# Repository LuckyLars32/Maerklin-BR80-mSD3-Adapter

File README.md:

# Maerklin-BR80-mSD3-Adapter
Adapterplatiene und Schallkapsel für den Einbau eines mSD3 Decoders in die Märklin BR 80.   
Die Platine habe ich mit KiCAD Version 7.X erstellt.   
Die Schallkapsel habe ich mit einer 0.4er Düse, 0.2mm Layerhöhe und 50% Infill gedruckt.   

# Materialliste / BOM:
2x LED 3.0mm (Warm-) weiß    
2x Widerstand 2,2 - 3,3 kΩ Bauform 1206 (3216 metrisch) je nach Präferenz und LED    
1x 24 Pin Steckleiste (Push-Pull) gerade mit 1,27mm Raster   
1x Keramikkondensator 1206 (3216 metrisch) 1UF   
1x Märklin mSD3 oder anderer Sounddecoder mit NEM 660 Schnitstelle   
1x 15x11x3mm Lautsprecher 4-8 Ohm   

# Zusammenbau
Einbauseite immer wie Bedruckung auf der Platiene.   
Die Wiederstände R1, R2, R3, R4 werden mit den 4x Widerstand 2,2 kΩ Bauform 0207 bestückt.   
Die NEM660 Schnittstelle wird mit der 24 Pin Steckleiste mit 1,27mm Raster bestückt.   
Der Keramikkondensator 1206 mit 1UF muss auf die Pads neben R1 und AUX4

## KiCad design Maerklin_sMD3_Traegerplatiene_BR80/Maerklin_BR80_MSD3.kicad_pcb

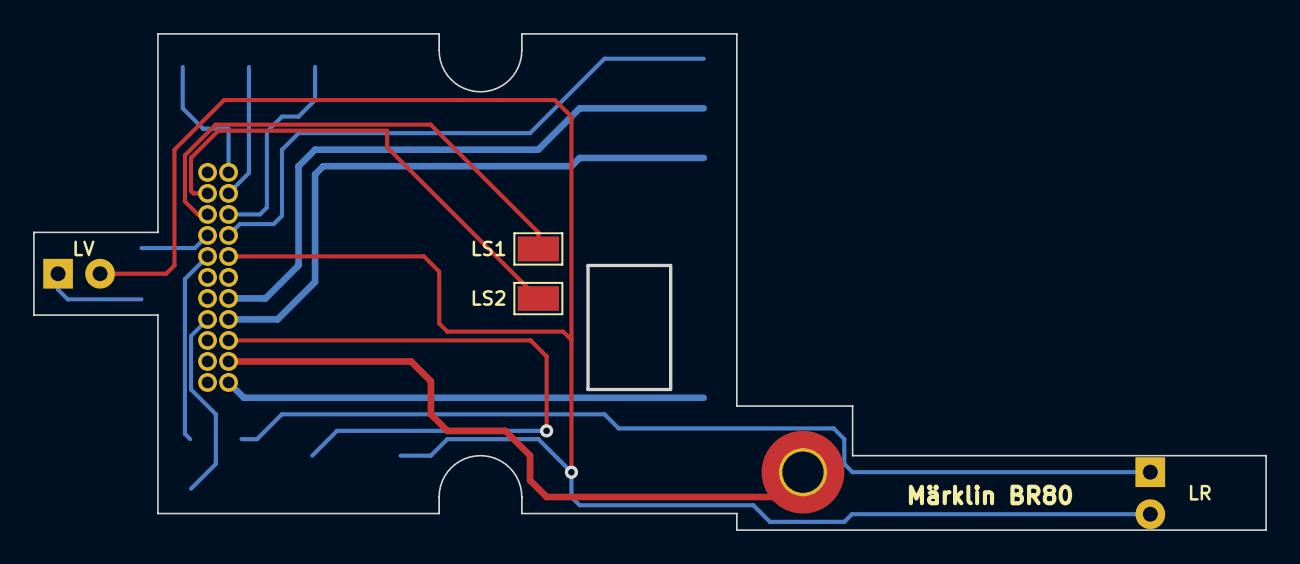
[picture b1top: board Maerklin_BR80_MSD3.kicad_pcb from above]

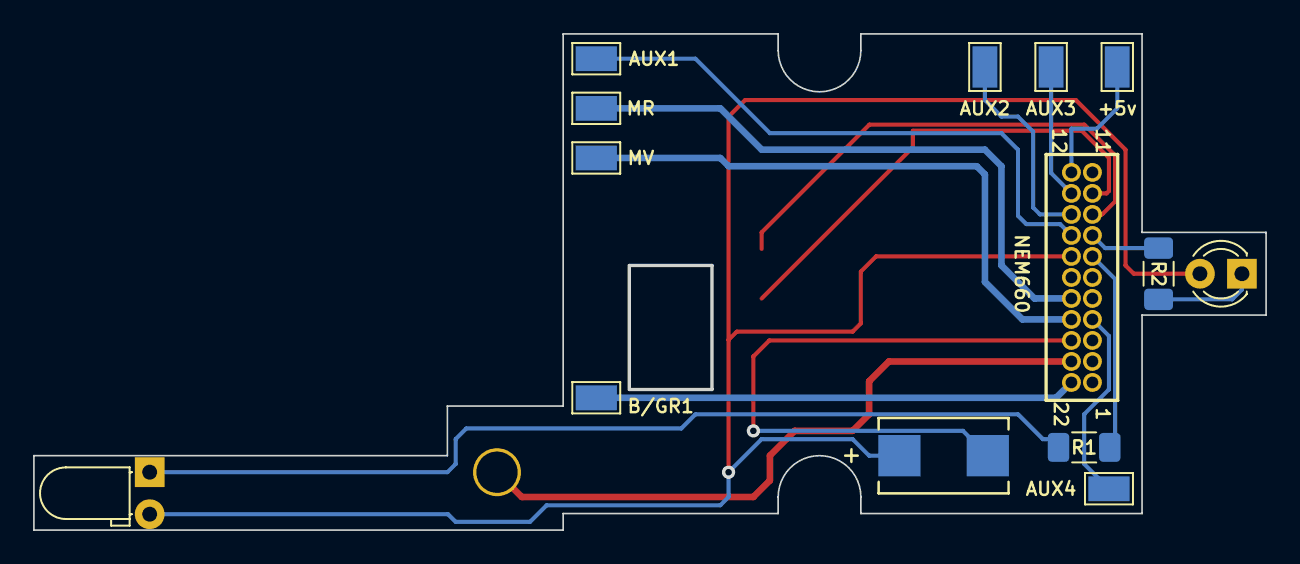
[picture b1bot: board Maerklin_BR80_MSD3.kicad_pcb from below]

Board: 2 copper layers, 74.5 x 30.0 mm, 17 parts (14 on the bottom side), 17 nets.

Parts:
+5v: +5v; TestPoint_Pad_1.5x2.5mm
AUX1: AUX1; TestPoint_Pad_1.5x2.5mm
AUX2: AUX2; TestPoint_Pad_1.5x2.5mm
AUX3: AUX3; TestPoint_Pad_1.5x2.5mm
AUX4: AUX4; TestPoint_Pad_1.5x2.5mm
B/GR1: B/GR; TestPoint_Pad_1.5x2.5mm
C1: T491X108K006AT; CAPMP7.6X4.3_4.3N_KEM
LR: LED Hinten; LED_D3.0mm_Horizontal_O1.27mm_Z2.0mm_Clear
LS1, LS2: LS; TestPoint_Pad_1.5x2.5mm
LV: LED Vorne; LED_D3.0mm_Clear
MR: MR; TestPoint_Pad_1.5x2.5mm
MV: MV; TestPoint_Pad_1.5x2.5mm
NEM660: SAMTEC-FTS-111-01-X-D
O/GL1: O/GL; MountingHole_2.5mm_Pad_TopOnly
R1, R2: R_1206_3216Metric_Pad1.30x1.75mm_HandSolder

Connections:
0/GL: NEM660.21, O/GL1.1
+5v: +5v.1, NEM660.12
+Ub: C1.1, LR.2 (A), LV.2 (A), NEM660.16
AUX1: AUX1.1, NEM660.15
AUX2: AUX2.1, NEM660.14
AUX3: AUX3.1, NEM660.13
AUX4: AUX4.1, NEM660.4
B/GR: B/GR1.1, NEM660.22
GND: C1.2, NEM660.20
LR: LR.1 (K), R1.1
LS1: LS2.1, NEM660.10
LS2: LS1.1, NEM660.9
LV: LV.1 (K), R2.1
MR: MR.1, NEM660.18
MV: MV.1, NEM660.19
unnamed: NEM660.7, R1.2
unnamed: NEM660.8, R2.2
